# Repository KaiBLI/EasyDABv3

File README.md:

# EasyDABv3
Prototype EasyDABv3 Board Map and Schematic

This is an unfinished prototype and we are missing firmware for the SoC and FPGA for this project. I am uploading this here for preservation in case anyone fancies a go at resolving the existing issues with this prototype and to design firmware. 

Even with the original firmware for this board, there are existing incompatibilities between the FPGA and the SoC that may cause some 'problems'. If you need a DAB modulator, check out https://github.com/KaiBLI/EasyDABv2 

Board Design and Photos Credit to Sergiy https://tipok.org.ua/

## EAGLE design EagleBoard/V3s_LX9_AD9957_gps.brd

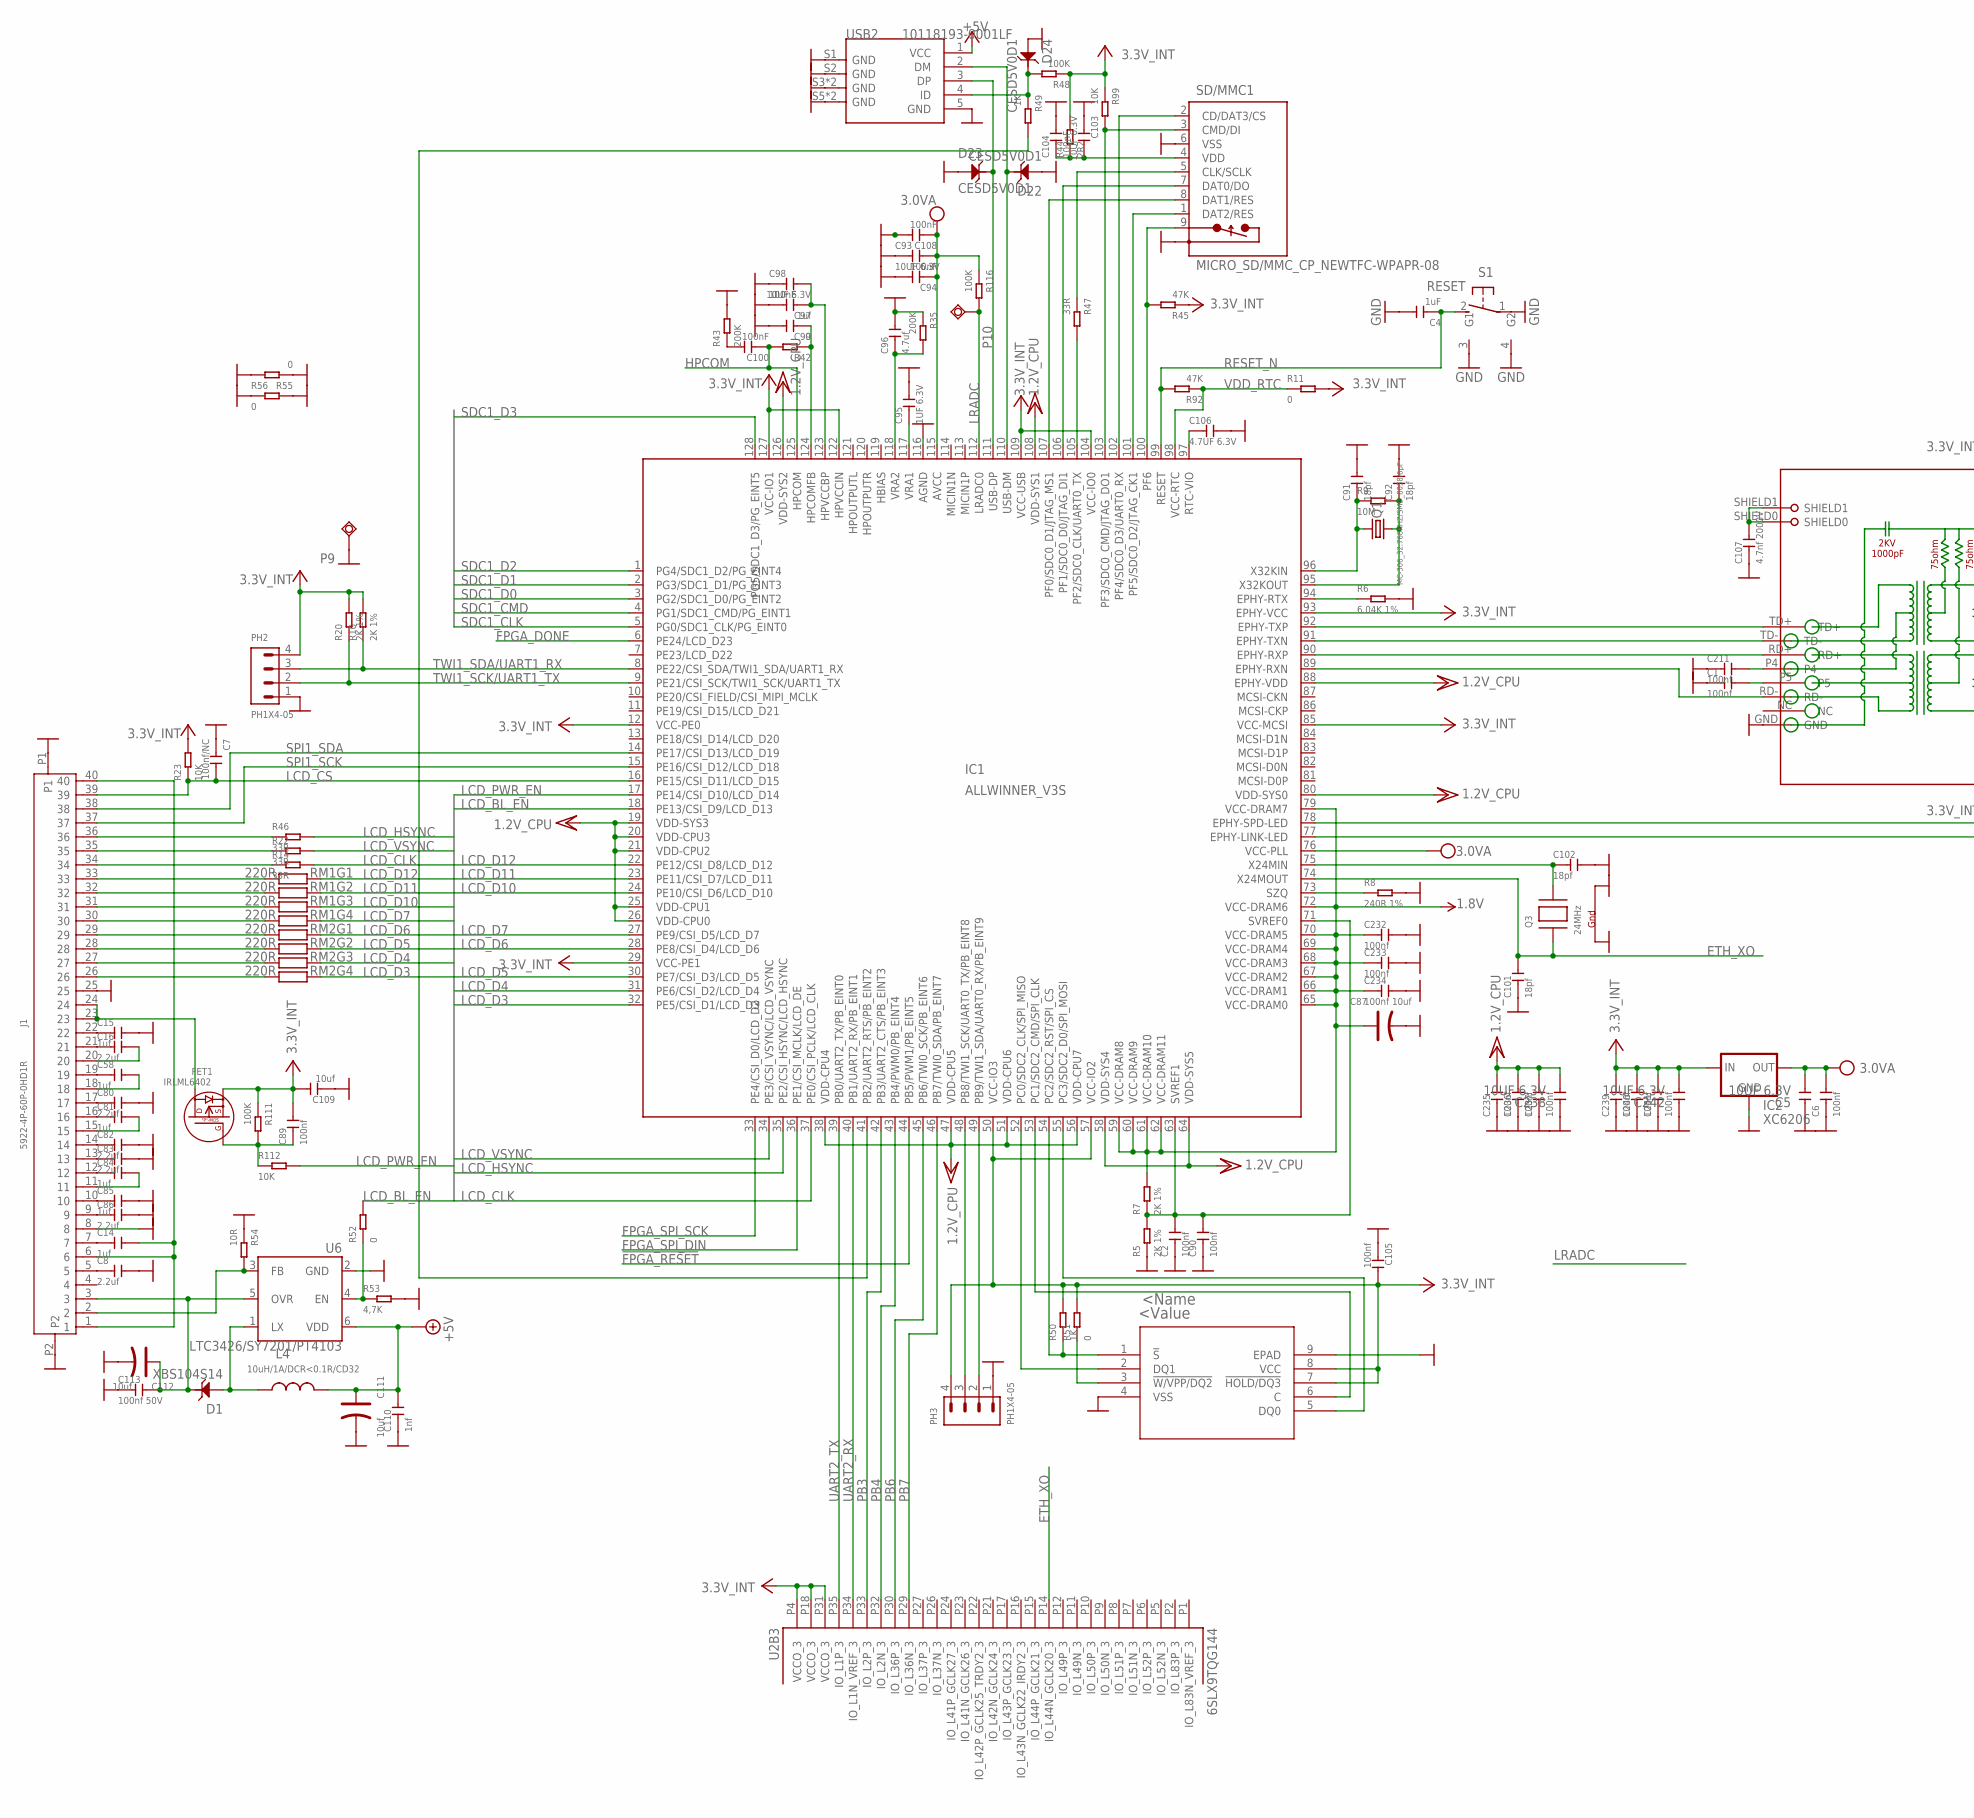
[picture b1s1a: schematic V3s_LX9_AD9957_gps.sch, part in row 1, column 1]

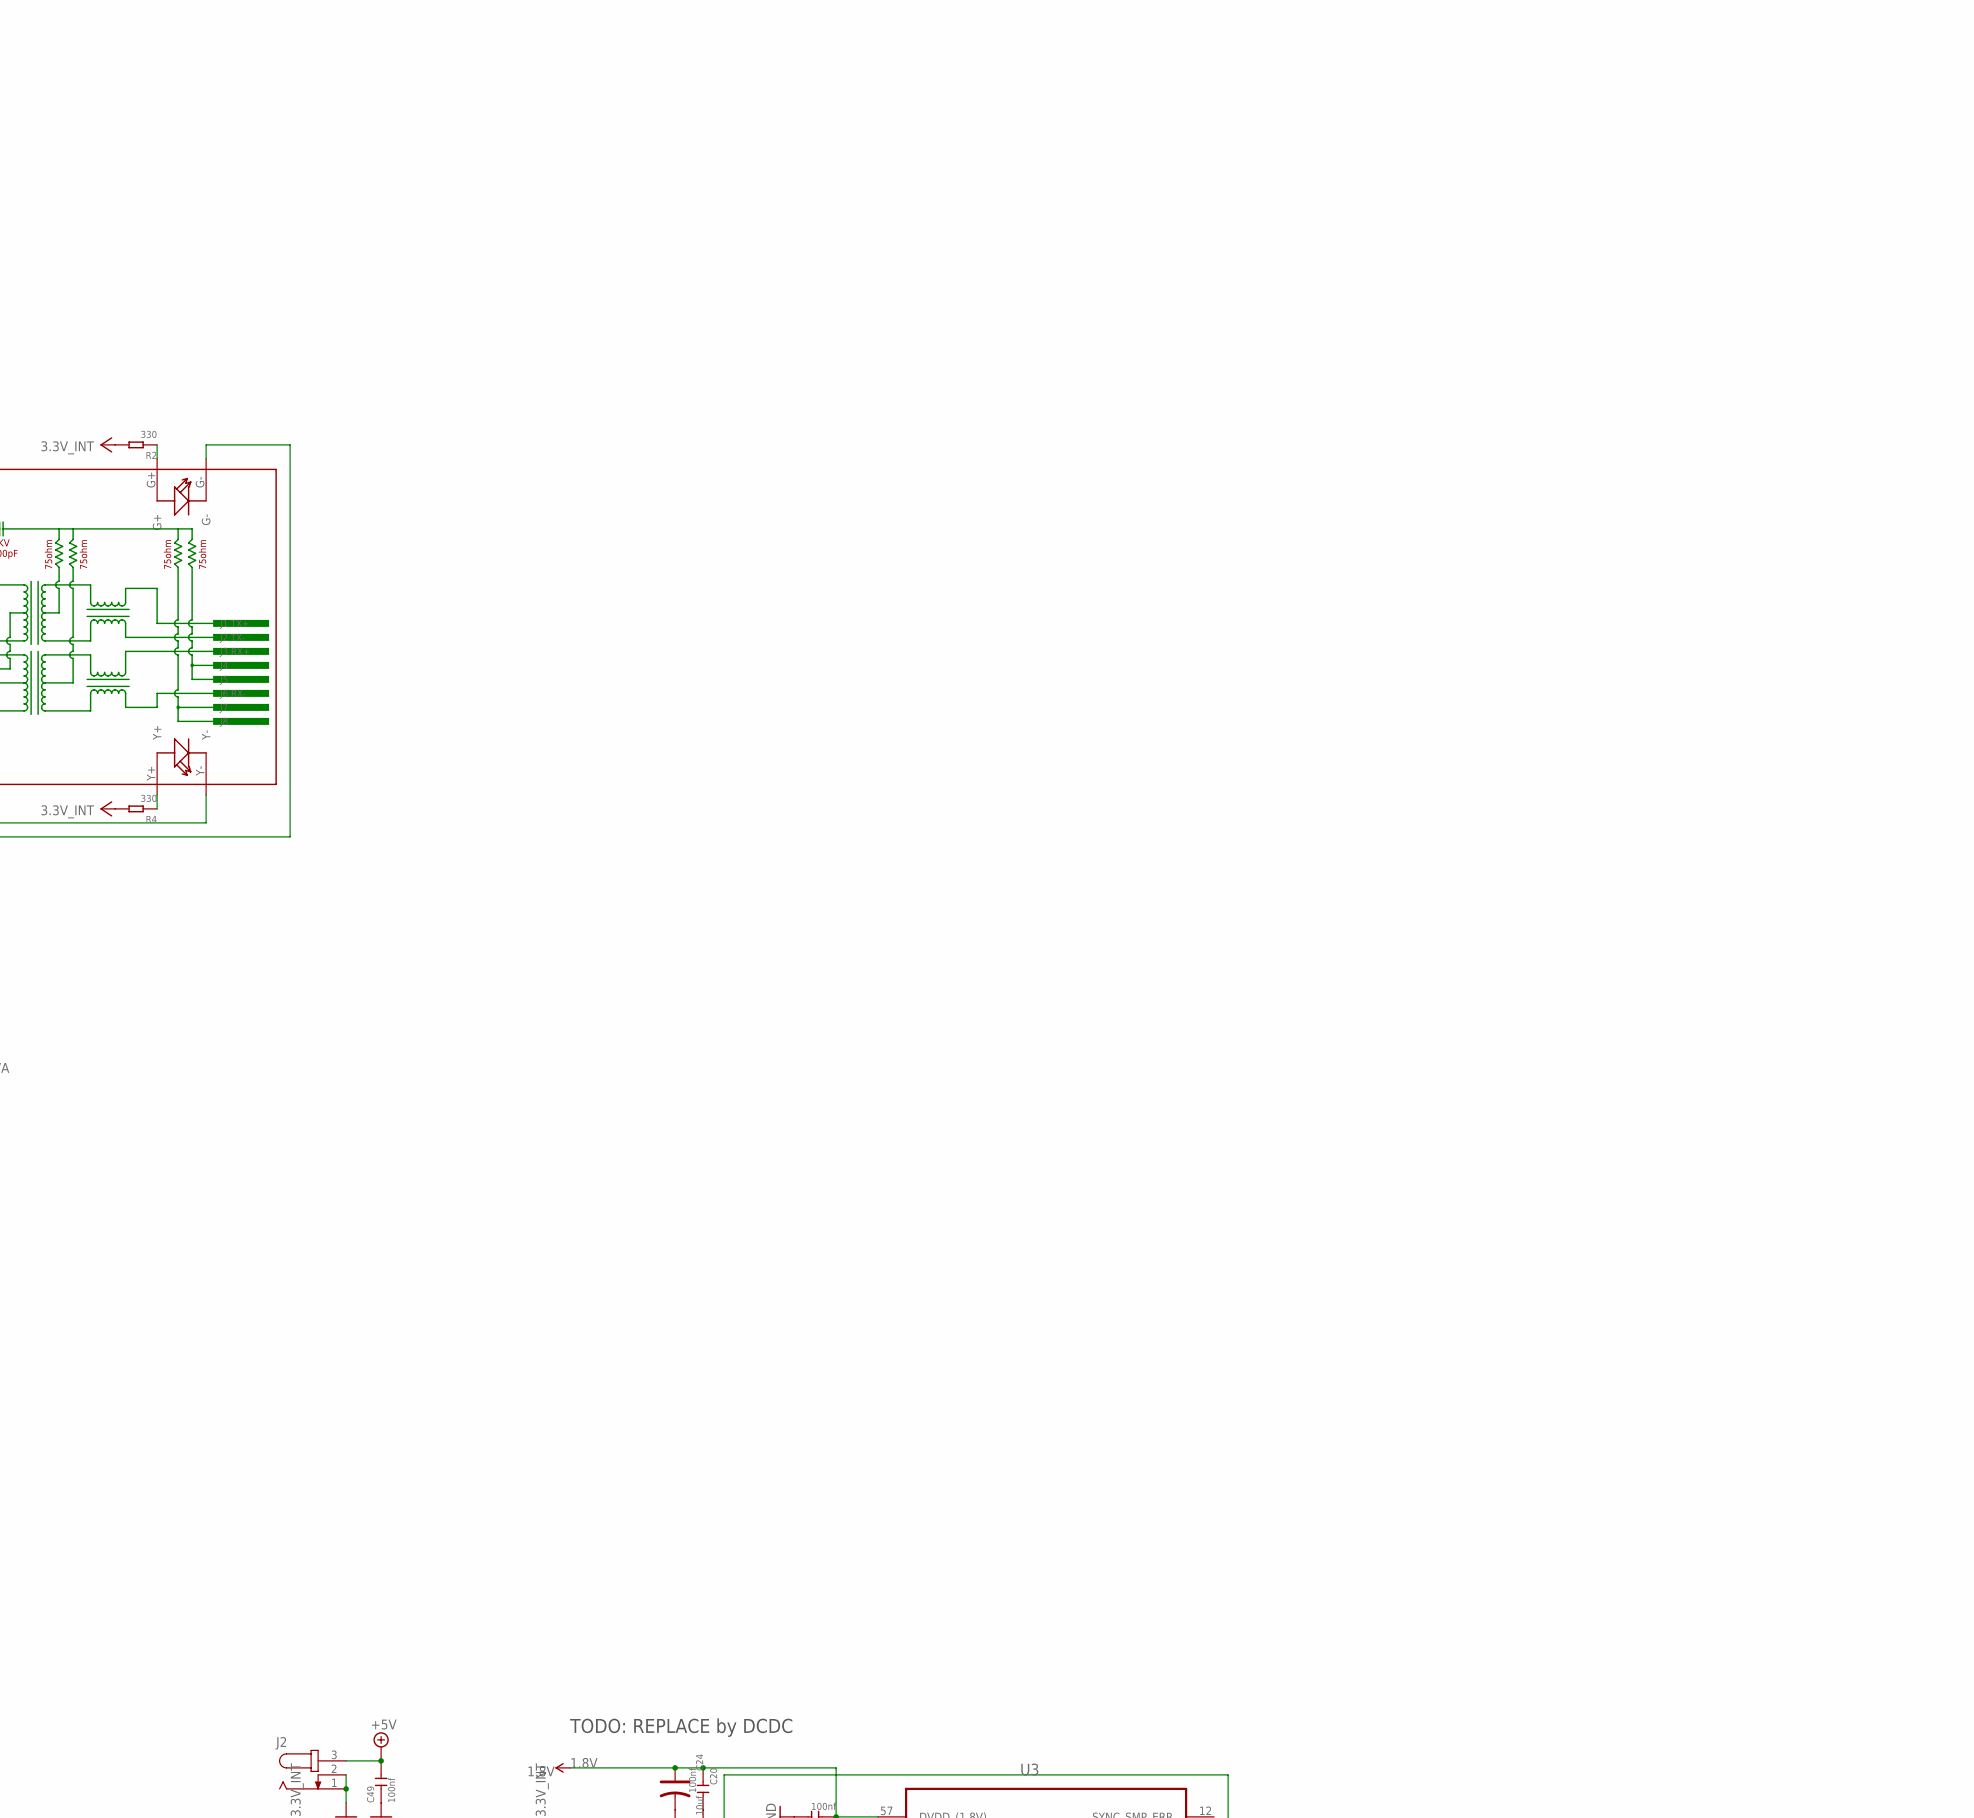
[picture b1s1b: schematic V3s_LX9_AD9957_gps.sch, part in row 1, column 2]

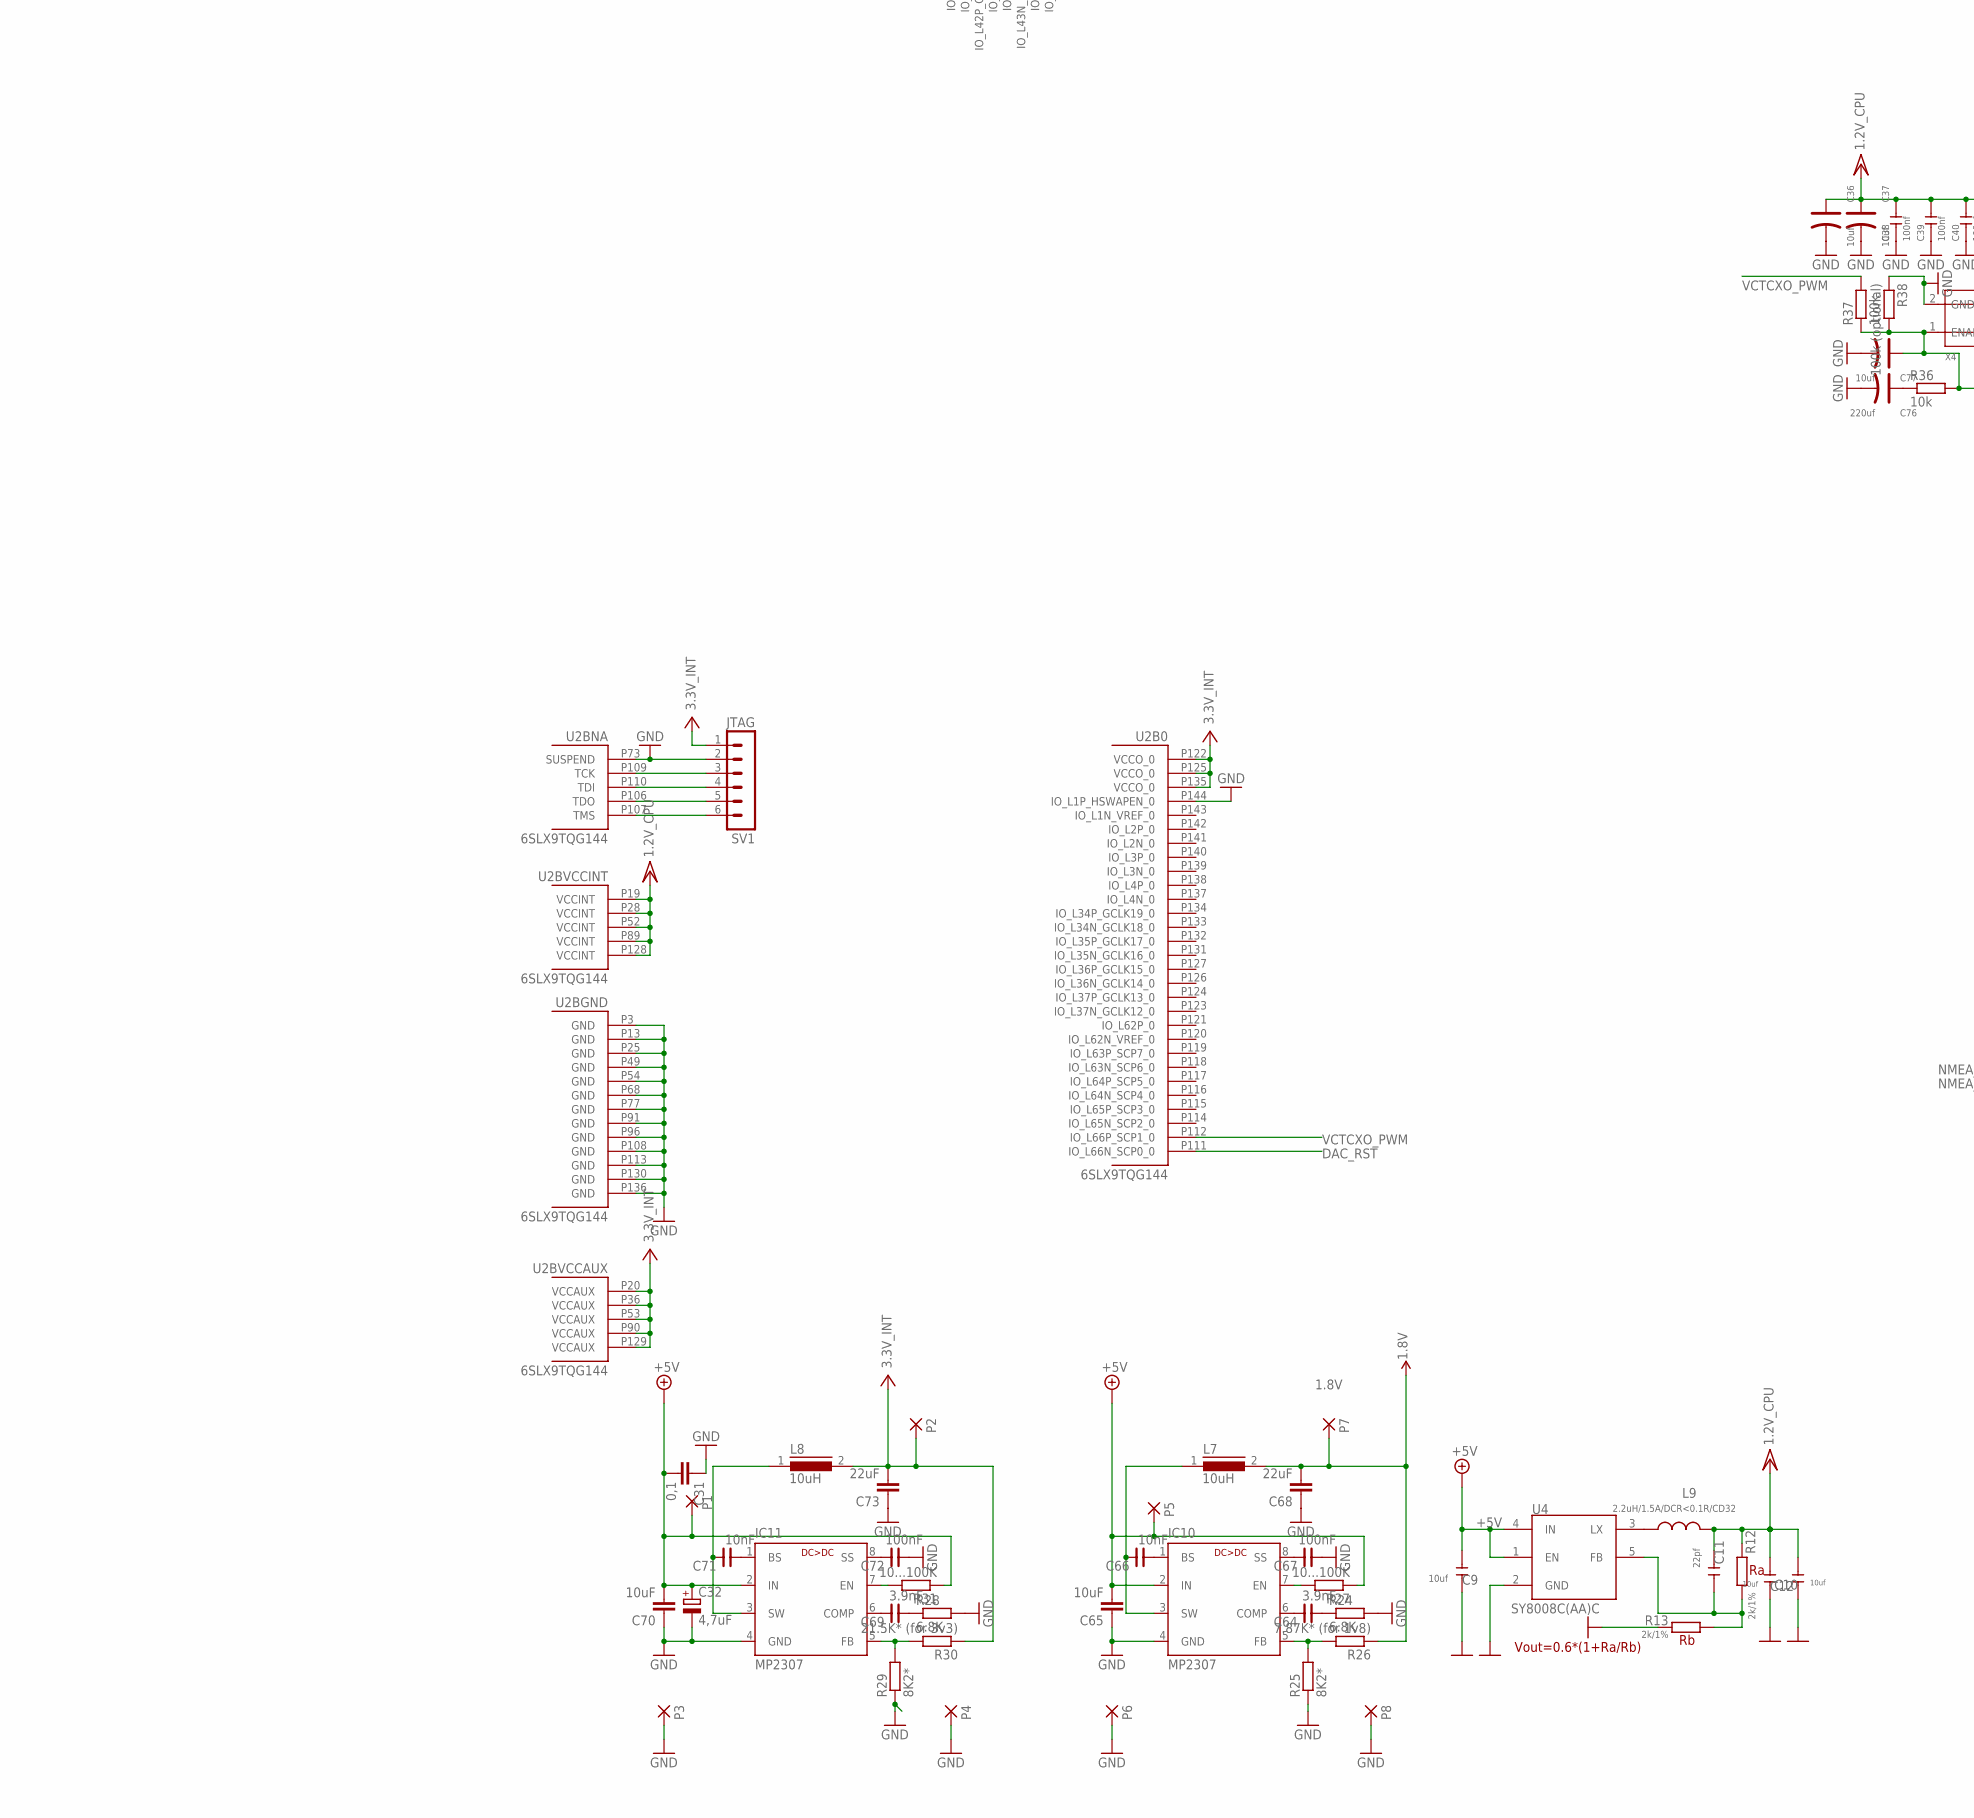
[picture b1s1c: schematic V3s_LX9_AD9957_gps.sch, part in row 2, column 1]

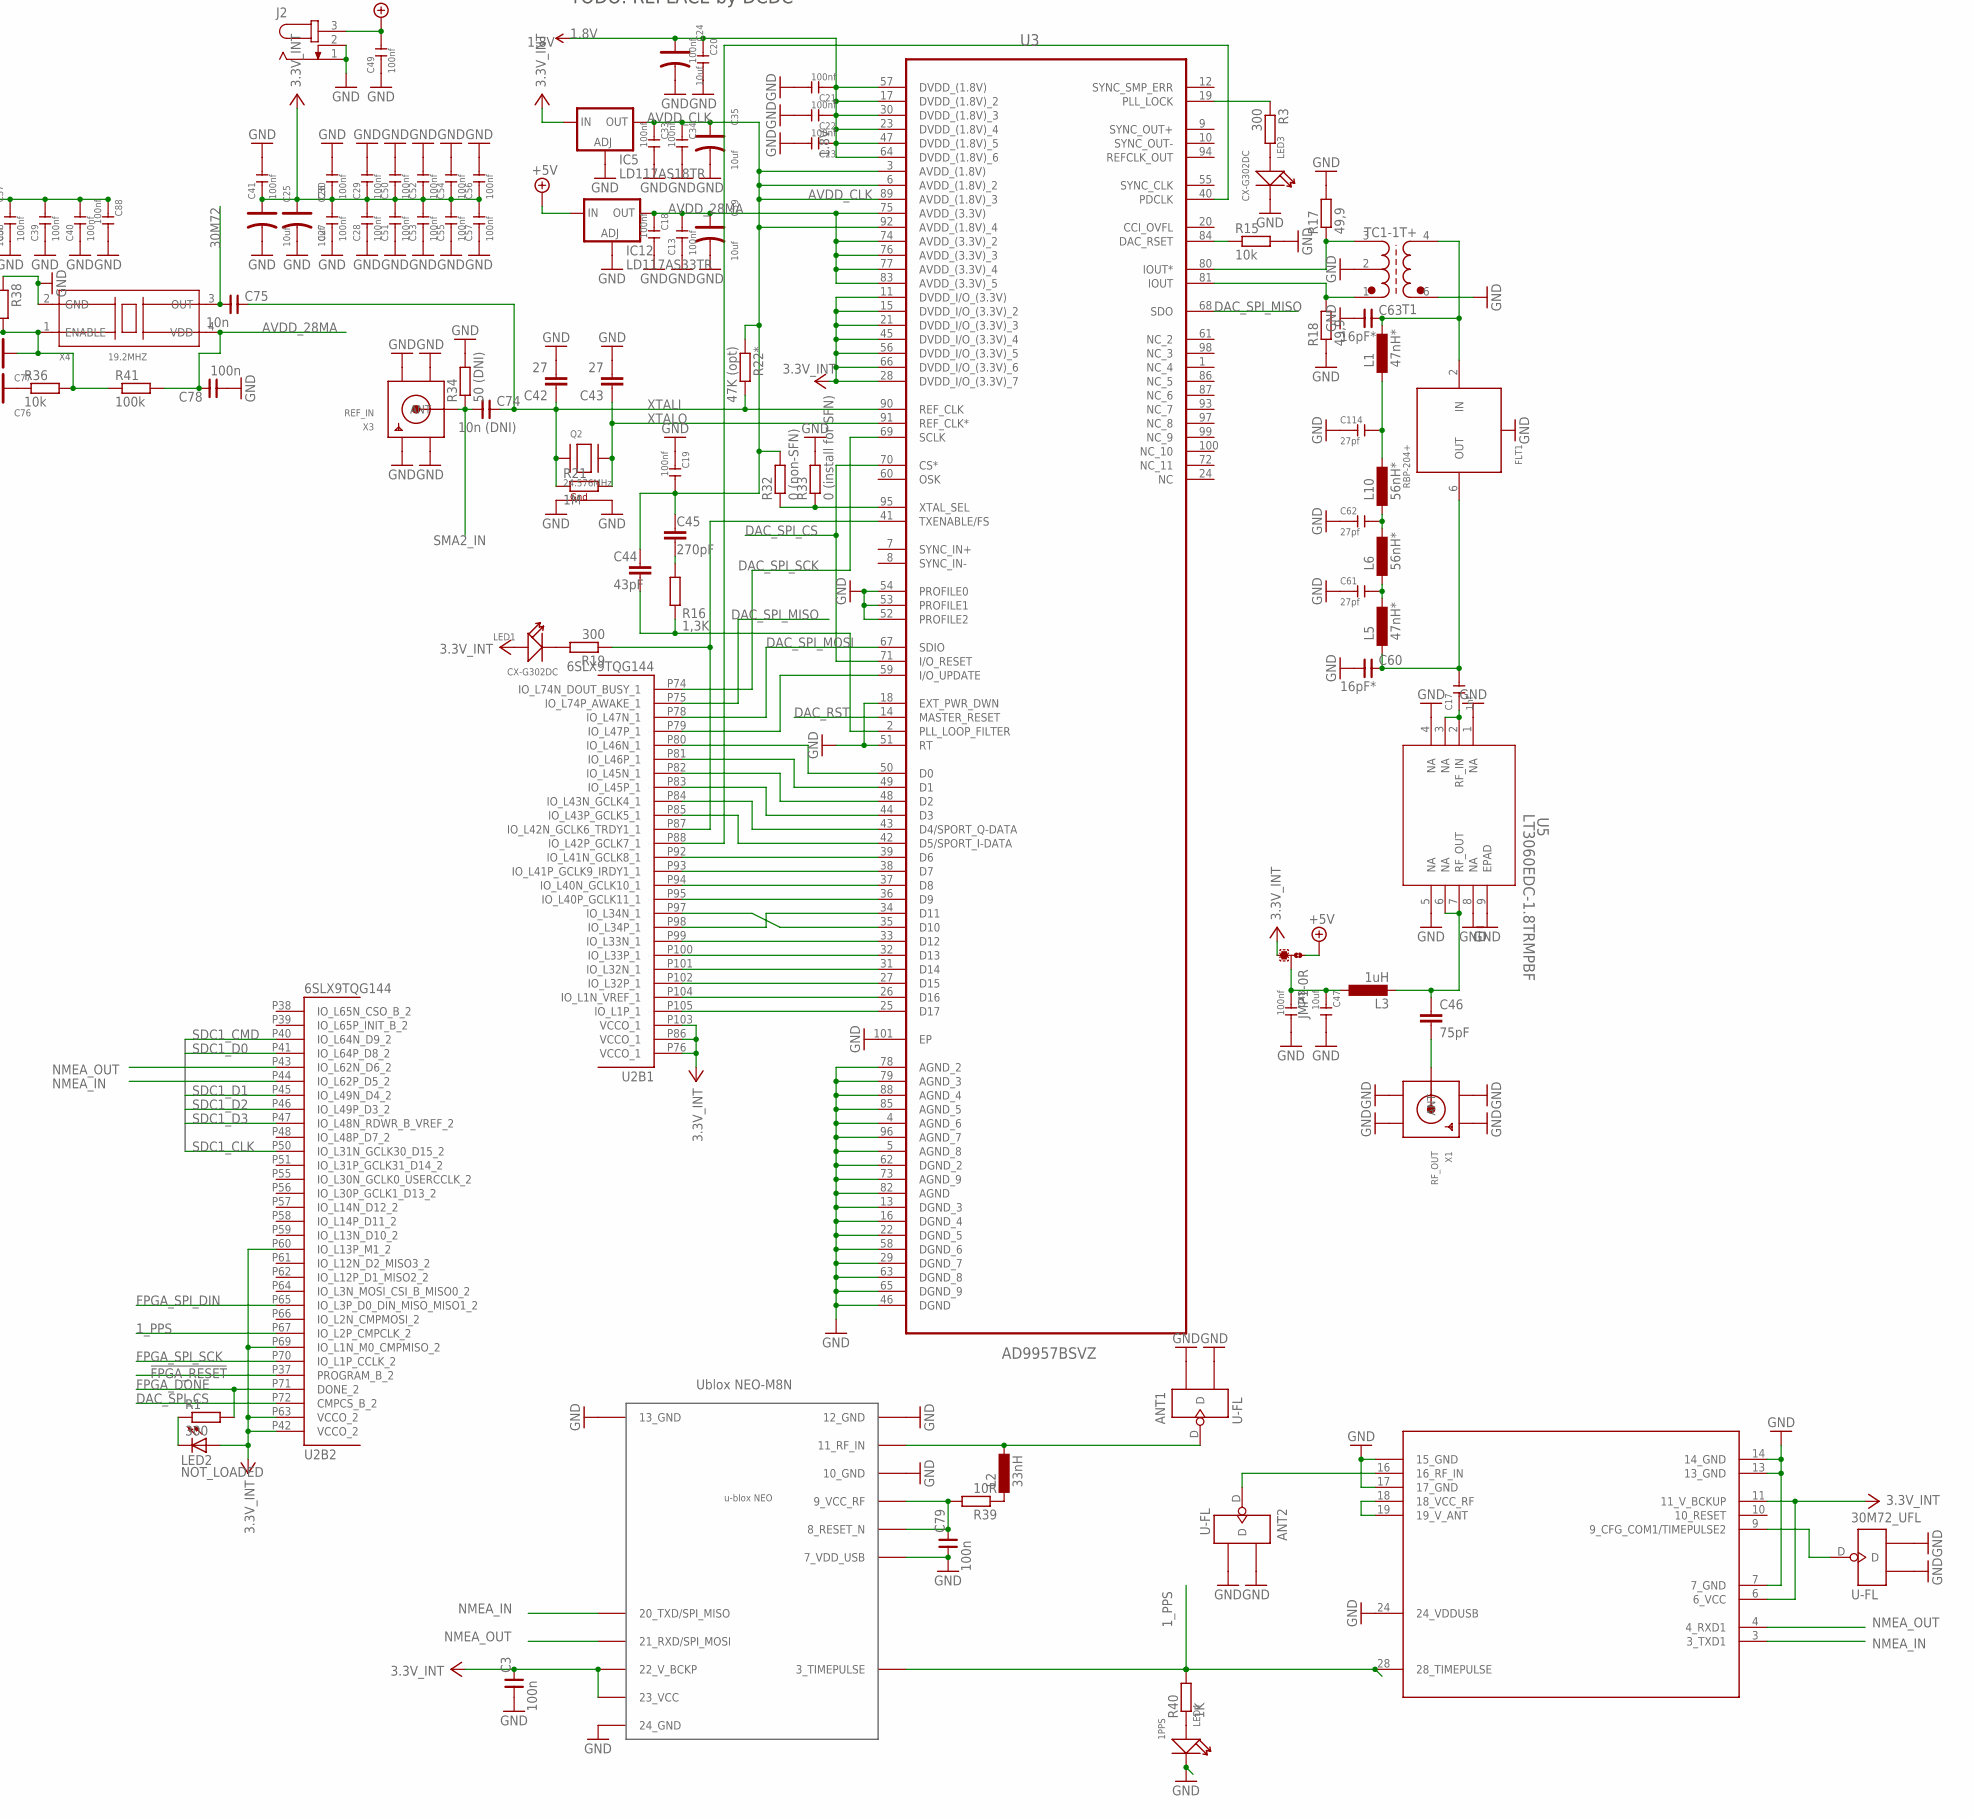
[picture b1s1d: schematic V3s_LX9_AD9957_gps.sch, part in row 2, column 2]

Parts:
30M72_UFL: U-FL; U-FL3P-SMD-2.6X2.6X1.0MM
ANT1, ANT2: U-FL; U-FL3P-SMD-2.6X2.6X1.0MM
C1, C2, C6, C23, C30, C38, C39, C40, C50, C52, C53, C55, C56, C88, C89, C90, C105, C211, C232, C233, C234, C235, C236, C237, C239, C240, C241: 100nf; C0603
C3, C78, C79: 100n; 0603
C4: 1uF; C0603
C5, C93, C97, C103, C238, C242: 10UF 6.3V; C0603
C7: 100nf/NC; C0603
C8, C16, C80, C82, C83, C86: 2.2uf; C0603
C9, C10, C12: 10uf; C0603
C11: 22pf; C0603
C13, C18, C19, C20, C21, C22, C27, C28, C29, C33, C34, C41, C48, C49, C51, C54, C57: 100nf; C0805
C14, C15, C58, C81, C84, C85, C99: 1uf; C0603
C17, C110: 1nf; C0603
C24, C25, C26, C35, C36, C37, C59, C77, C87, C111, C112: 10uf; AVX-A
C31: 0,1; C0805
C32: 4,7uF; A/3216-18R
C42, C43: 27; C0805
C44: 43pF; C0805
C45: 270pF; C0805
C46: 75pF; C0805
C47, C109: 10uf; C0805
C60, C63: 16pF*; 0603
C61, C62, C114: 27pf; C0603
C64, C69: 3.9nF; 0603
C65, C70: 10uF; C1206
C66, C71: 10nF; 0603
C67, C72: 100nF; 0603
C68, C73: 22uF; C1206
C74: 10n (DNI); 0603
C75: 10n; 0603
C76: 220uf; AVX-D
C91, C92, C101, C102: 18pf; C0603
C94, C98, C100, C104, C108: 100nF; C0603
C95: 1UF 6.3V; C0603
C96: 4.7uf; C0603
C106: 4.7UF 6.3V; C0603
C107: 4.7nf 2000V; C1206
C113: 100nf 50V; C0603
D1: XBS104S14; SOD-123
D22, D23, D24: CESD5V0D1; SOD-123
FET1: IRLML6402; SOT23
FLT1: RBP-204+; GP731
IC1: ALLWINNER_V3S; ELQFP128
IC2: XC6206; SOT23
IC5: LD117AS18TR; SOT223
IC10, IC11: MP2307; SO8
IC12: LD117AS33TR; SOT223
J1: 5922-4P-60P-0HD1R; FPCE40-SMD-0.5-90D
J2: JACK-PLUG0; SPC4077
JMP1: 0R-JUMPA; A0R-JMP
L1, L5: 47nH*; INDC1608X95N
L2: 33nH; INDC1608X95N
L3: 1uH; L3216C
L4: 10uH/1A/DCR<0.1R/CD32; CD32
L6, L10: 56nH*; INDC1608X95N
L7, L8: 10uH; DR74
L9: 2.2uH/1.5A/DCR<0.1R/CD32; CD32
LED1, LED3: CX-G302DC; LED2-2.54-D3.0MM
LED2: NOT_LOADED; CHIPLED_1206
LED4: 1PPS; LED2-2.54-D3.0MM
P1, P2, P3, P4, P5, P6, P7, P8: 1,6/0,8
P9, P10: TESTPADTESTPAD30/30; TESTPAD_30-ROUND
PH2, PH3: PH1X4-05; PH005-1-4
Q1: MC-306_32.768KHZ/SMD_8038/6pF; MC-306
Q2: 24.576MHz; NX3225
Q3: 24MHz; NX3225
R1, R3, R19: 300; M0805
R2, R4: 330; R0603
R5, R7, R10, R20: 2K 1%; R0603
R6: 6.04K 1%; R0603
R8: 240R 1%; R0603
R9: 10M; R0603
R11, R42, R51, R52, R55, R56: 0; R0603
R12, R13: 2k/1%; R0603_5MIL_DWS
R14, R22, R46, R47: 33R; R0603
R15: 10k; R0805
R16: 1,3K; R0805
R17, R18: 49,9; R0805
R21: 1M; R0805
R22*: 47K (opt); R0603
R23: 10K; R0402
R24, R28: 6.8K; R0603
R25, R29: 8K2*; R0603
R26: 7.87K* (for 1v8); R0603
R27, R31: 10...100K; R0603
R30: 21.5K* (for 3v3); R0603
R32: 0 (non-SFN); R0402
R33: 0 (install for SFN); R0402
R34: 50 (DNI); R0402
R35, R43: 200K; R0603
R36: 10k; R0603
R37, R41: 100k; R0603
R38: 100k (optional); R0603
R39: 10R; R0402
R40: 1K; R0402
R44: 2R2; R0603
R45, R92: 47K; R0603
R48, R111, R116: 100K; R0603
R49, R50: 1K; R0603
R53: 4,7K; R0603
R54: 10R; R0603
R99, R112: 10K; R0603
RJ1: HR911105A
RM1, RM2: 220R; R_MATRIX_4_0402_25X625
S1: RESET; B3F-31XX
SD/MMC1: MICRO_SD/MMC_CP_NEWTFC-WPAPR-08; TFC-WPAPR-08
SV1: JTAG; MA06-1
T1: TC1-1T+; AT224-3
U1: N25Q256A13EF840EMIC; MIC-VFDFPN-8_8X6-M
U2: 6SLX9TQG144; TQ144
U3: AD9957BSVZ; QFP50P1600X1600X120-101N
U4: SY8008C(AA)C; SOT23-5
U5: LT3060EDC-1.8TRMPBF; DFN-8_DC
U6: LTC3426/SY7201/PT4103; SOT23-6
U10: NEO-M8
U11: UBLOX_LEA-6; UBLOX_LEA-6T
USB2: 10118193-0001LF; MICRO-USB5+6P-SMD-0.65-B
X1: RF_OUT; SMA90_DIP
X3: REF_IN; W5500_LX9_AD9957_SMA_EDGELAUNCH_UFL
X4: 19.2MHZ; X4-SMD-3.2X2.5X0.7MM

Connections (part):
1.8V: C20.1, C21.1, C22.1, C23.1, C24.+, C68.2, C87.+, C232.1, C233.1, C234.1, IC1.59 (VCC-DRAM8), IC1.60 (VCC-DRAM9), IC1.61 (VCC-DRAM10), IC1.62 (VCC-DRAM11), IC1.65 (VCC-DRAM0), IC1.66 (VCC-DRAM1), IC1.67 (VCC-DRAM2), IC1.68 (VCC-DRAM3), IC1.69 (VCC-DRAM4), IC1.70 (VCC-DRAM5), IC1.72 (VCC-DRAM6), IC1.79 (VCC-DRAM7), L7.2, P7.1, R7.2, R26.1, U3.17 (DVDD_(1.8V)_2), U3.23 (DVDD_(1.8V)_4), U3.30 (DVDD_(1.8V)_3), U3.47 (DVDD_(1.8V)_5), U3.57 (DVDD_(1.8V)), U3.64 (DVDD_(1.8V)_6)
1_PPS: R40.2, U2.P67 (IO_L2P_CMPCLK_2), U10.3 (3_TIMEPULSE), U11.28 (28_TIMEPULSE)
30M72: C75.1, X4.3 (OUT)
!FPGA_RESET: IC1.44 (PB5/PWM1/PB_EINT5), U2.P37 (PROGRAM_B_2)
+5V: C9.1, C31.2, C32.+, C49.2, C65.2, C70.2, C110.2, C111.+, IC10.2 (IN), IC11.2 (IN), IC12.3 (IN), J2.3, JMP1.1, L4.1, P1.1, P5.1, R27.1, R31.1, U4.1 (EN), U4.4 (IN), U6.6 (VDD), USB2.1 (VCC)
AVDD_28MA: C13.2, C18.1, C59.+, C78.2, IC12.4 (OUT), R41.2, U3.74 (AVDD_(3.3V)_2), U3.75 (AVDD_(3.3V)), U3.76 (AVDD_(3.3V)_3), U3.77 (AVDD_(3.3V)_4), U3.83 (AVDD_(3.3V)_5), X4.4 (VDD)
AVDD_CLK: C19.2, C33.1, C34.1, C35.+, C44.1, C45.1, IC5.4 (OUT), R22*.1, R32.2, U3.3 (AVDD_(1.8V)), U3.6 (AVDD_(1.8V)_2), U3.89 (AVDD_(1.8V)_3), U3.92 (AVDD_(1.8V)_4)
DAC_RST: U2.P111 (IO_L66N_SCP0_0), U3.14 (MASTER_RESET)
DAC_SPI_CS: U2.P72 (CMPCS_B_2), U3.70 (CS*), U3.71 (I/O_RESET)
DAC_SPI_MISO: U2.P75 (IO_L74P_AWAKE_1), U3.68 (SDO)
DAC_SPI_MOSI: U2.P78 (IO_L47N_1), U3.67 (SDIO)
DAC_SPI_SCK: U2.P74 (IO_L74N_DOUT_BUSY_1), U3.69 (SCLK)
ETH_XO: C101.2, IC1.74 (X24MOUT), Q3.1 (X1), U2.P14 (IO_L44N_GCLK20_3)
FPGA_DONE: IC1.6 (PE24/LCD_D23), R1.2, U2.P71 (DONE_2)
FPGA_SPI_DIN: IC1.36 (PE1/CSI_MCLK/LCD_DE), U2.P65 (IO_L3P_D0_DIN_MISO_MISO1_2)
FPGA_SPI_SCK: IC1.33 (PE4/CSI_D0/LCD_D2), U2.P70 (IO_L1P_CCLK_2)
GND: 30M72_UFL.GND1, 30M72_UFL.GND2, ANT1.GND1, ANT1.GND2, ANT2.GND1, ANT2.GND2, C1.1, C2.1, C3.1, C4.2, C5.1, C6.1, C7.1, C8.2, C9.2, C10.2, C12.2, C13.1, C15.2, C18.2, C19.1, C20.2, C21.2, C22.2, C23.2, C24.-, C25.-, C26.-, C27.1, C28.1, C29.2, C30.2, C31.1, C32.-, C33.2, C34.2, C35.-, C36.-, C37.-, C38.1, C39.1, C40.1, C41.2, C42.2, C43.2, C47.2, C48.2, C49.1, C50.2, C51.1, C52.2, C53.1, C54.2, C55.1, C56.2, C57.1, C59.-, C60.1, C61.1, C62.1, C63.1, C65.1, C67.1, C68.1, C70.1, C72.1, C73.1, C76.-, C77.-, C78.1, C79.1, C80.2, C82.2, C83.2, C85.2, C86.2, C87.-, C88.2, C90.1, C91.2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
GPSDO_OUT_30M72: 30M72_UFL.D, U11.9 (9_CFG_COM1/TIMEPULSE2)
HPCOM: C100.1, IC1.125 (HPCOM), R42.2
LCD_BL_EN: IC1.18 (PE13/CSI_D9/LCD_D13), R52.2
LCD_CLK: IC1.37 (PE0/CSI_PCLK/LCD_CLK), R14.2
LCD_CS: C7.2, IC1.16 (PE15/CSI_D11/LCD_D15), J1.39, R23.1
LCD_D3: IC1.32 (PE5/CSI_D1/LCD_D3), RM2.4.1 (1)
LCD_D4: IC1.31 (PE6/CSI_D2/LCD_D4), RM2.3.1 (1)
LCD_D5: IC1.30 (PE7/CSI_D3/LCD_D5), RM2.2.1 (1)
LCD_D6: IC1.28 (PE8/CSI_D4/LCD_D6), RM2.1.1 (1)
LCD_D7: IC1.27 (PE9/CSI_D5/LCD_D7), RM1.4.1 (1)
LCD_D10: IC1.24 (PE10/CSI_D6/LCD_D10), RM1.3.1 (1)
LCD_D11: IC1.23 (PE11/CSI_D7/LCD_D11), RM1.2.1 (1)
LCD_D12: IC1.22 (PE12/CSI_D8/LCD_D12), RM1.1.1 (1)
LCD_HSYNC: IC1.35 (PE2/CSI_HSYNC/LCD_HSYNC), R46.2
LCD_PWR_EN: IC1.17 (PE14/CSI_D10/LCD_D14), R112.2
LCD_VSYNC: IC1.34 (PE3/CSI_VSYNC/LCD_VSYNC), R22.2
LRADC: IC1.112 (LRADC0), P10.1, R116.2
unnamed: SV1.6, U2.P107 (TMS)
unnamed: SV1.5, U2.P106 (TDO)
unnamed: SV1.4, U2.P110 (TDI)
unnamed: SV1.3, U2.P109 (TCK)
unnamed: LED2.C, R1.1
unnamed: C62.2, L6.2, L10.1
unnamed: U2.P105 (IO_L1P_1), U3.25 (D17)
unnamed: C14.2, J1.1, J1.6, J1.40
unnamed: U2.P88 (IO_L42P_GCLK7_1), U3.40 (PDCLK)
unnamed: R19.1, U2.P87 (IO_L42N_GCLK6_TRDY1_1), U3.41 (TXENABLE/FS)
unnamed: U2.P85 (IO_L43P_GCLK5_1), U3.42 (D5/SPORT_I-DATA)
unnamed: U2.P84 (IO_L43N_GCLK4_1), U3.43 (D4/SPORT_Q-DATA)
unnamed: U2.P83 (IO_L45P_1), U3.44 (D3)
unnamed: U2.P82 (IO_L45N_1), U3.48 (D2)
unnamed: U2.P92 (IO_L41N_GCLK8_1), U3.39 (D6)
unnamed: U2.P93 (IO_L41P_GCLK9_IRDY1_1), U3.38 (D7)
unnamed: U2.P94 (IO_L40N_GCLK10_1), U3.37 (D8)
unnamed: U2.P95 (IO_L40P_GCLK11_1), U3.36 (D9)
unnamed: U2.P98 (IO_L34P_1), U3.34 (D11)
unnamed: U2.P97 (IO_L34N_1), U3.35 (D10)
unnamed: U2.P99 (IO_L33N_1), U3.33 (D12)
unnamed: U2.P100 (IO_L33P_1), U3.32 (D13)
unnamed: U2.P101 (IO_L32N_1), U3.31 (D14)
unnamed: U2.P102 (IO_L32P_1), U3.27 (D15)
unnamed: U2.P104 (IO_L1N_VREF_1), U3.26 (D16)
unnamed: U2.P79 (IO_L47P_1), U3.59 (I/O_UPDATE)
unnamed: C14.1, J1.7
unnamed: U2.P81 (IO_L46P_1), U3.49 (D1)
unnamed: LED3.A (+), R3.2
unnamed: R3.1, U3.19 (PLL_LOCK)
unnamed: R15.1, U3.84 (DAC_RSET)
unnamed: R17.1, T1.3 (S), U3.80 (IOUT*)
unnamed: R18.2, T1.1 (SD), U3.81 (IOUT)
unnamed: C63.2, FLT1.2 (IN), L1.2, T1.4
unnamed: U2.P80 (IO_L46N_1), U3.50 (D0)
unnamed: IC1.89 (EPHY-RXN), RJ1.RD-
unnamed: C211.2, RJ1.P4
unnamed: IC1.94 (EPHY-RTX), R6.1
unnamed: IC1.78 (EPHY-SPD-LED), RJ1.Y-
unnamed: IC1.77 (EPHY-LINK-LED), RJ1.G-
unnamed: R4.1, RJ1.Y+
unnamed: R2.1, RJ1.G+
unnamed: C2.2, C90.2, IC1.63 (SVREF1), IC1.71 (SVREF0), R5.2, R7.1
unnamed: IC1.73 (SZQ), R8.1
unnamed: C92.1, IC1.95 (X32KOUT), Q1.1, R9.2
unnamed: C91.1, IC1.96 (X32KIN), Q1.4 (2), R9.1
unnamed: D22.- (2), IC1.110 (USB-DM), USB2.2 (DM)
unnamed: D23.- (2), IC1.111 (USB-DP), USB2.3 (DP)
unnamed: C95.1, IC1.117 (VRA1)
unnamed: C96.1, IC1.118 (VRA2), R35.2
unnamed: C99.1, IC1.124 (HPCOMFB), R42.1
unnamed: C102.1, IC1.75 (X24MIN), Q3.3 (X2)
unnamed: U11.18 (18_VCC_RF), U11.19 (19_V_ANT)
unnamed: IC1.107 (PF0/SDC0_D1/JTAG_MS1), SD/MMC1.8 (DAT1/RES)
unnamed: IC1.106 (PF1/SDC0_D0/JTAG_DI1), SD/MMC1.7 (DAT0/DO)
unnamed: R47.1, SD/MMC1.5 (CLK/SCLK)
unnamed: IC1.103 (PF3/SDC0_CMD/JTAG_DO1), R99.2, SD/MMC1.3 (CMD/DI)
unnamed: IC1.102 (PF4/SDC0_D3/UART0_RX), SD/MMC1.2 (CD/DAT3/CS)
unnamed: IC1.101 (PF5/SDC0_D2/JTAG_CK1), SD/MMC1.1 (DAT2/RES)
unnamed: IC1.100 (PF6), R45.2, SD/MMC1.9 (CP_E)
unnamed: ANT1.D, L2.2, U10.11 (11_RF_IN)
unnamed: IC1.105 (PF2/SDC0_CLK/UART0_TX), R47.2
unnamed: D24.- (2), R48.2, R49.1, USB2.4 (ID)
unnamed: IC1.41 (PB2/UART2_RTS/PB_EINT2), R49.2
unnamed: IC1.92 (EPHY-TXP), RJ1.TD+
unnamed: IC1.91 (EPHY-TXN), RJ1.TD-
unnamed: IC1.90 (EPHY-RXP), RJ1.RD+
unnamed: L9.1, U4.3 (LX)
unnamed: C97.1, C98.2, IC1.123 (HPVCCBP)
unnamed: C8.1, J1.5
unnamed: R51.1, U1.3 (!W/VPP/DQ2)
unnamed: C11.2, R12.2, R13.1, U4.5 (FB)
unnamed: J1.33, RM1.1.2 (2)
unnamed: ANT2.D, U11.16 (16_RF_IN)
unnamed: C114.2, L1.1, L10.2
unnamed: C44.2, R16.2, U3.2 (PLL_LOOP_FILTER)
unnamed: J1.36, R46.1
unnamed: J1.35, R22.1
unnamed: J1.34, R14.1
unnamed: J1.32, RM1.2.2 (2)
unnamed: J1.31, RM1.3.2 (2)
unnamed: J1.30, RM1.4.2 (2)
unnamed: C45.2, R16.1
unnamed: C17.2, C60.2, FLT1.6 (OUT), L5.1
unnamed: J1.29, RM2.1.2 (2)
unnamed: C46.1, L3.2, U5.6 (NA), U5.7 (RF_OUT)
unnamed: C46.2, X1.ANTENNA (ANT)
unnamed: C47.1, C48.1, JMP1.2, L3.1
unnamed: LED1.K (-), R19.2
unnamed: L2.1, R39.1
unnamed: C61.2, L5.2, L6.1
unnamed: J1.28, RM2.2.2 (2)
unnamed: C79.2, R39.2, U10.8 (8_RESET_N), U10.9 (9_VCC_RF)
unnamed: LED4.A (+), R40.1
unnamed: J1.27, RM2.3.2 (2)
unnamed: J1.26, RM2.4.2 (2)
unnamed: C15.1, J1.22
unnamed: C17.1, U5.2 (RF_IN), U5.3 (NA)
unnamed: C64.2, IC10.6 (COMP)
unnamed: C64.1, R24.1
unnamed: C66.1, IC10.1 (BS)
unnamed: C66.2, IC10.3 (SW), L7.1
unnamed: C67.2, IC10.8 (SS)
unnamed: IC10.5 (FB), R25.2, R26.2
unnamed: R32.1, R33.1, U3.95 (XTAL_SEL)
unnamed: IC10.7 (EN), R27.2
unnamed: C100.2, R43.1
unnamed: C69.1, R28.1
unnamed: C69.2, IC11.6 (COMP)
unnamed: C71.1, IC11.1 (BS)
unnamed: C71.2, IC11.3 (SW), L8.1
unnamed: C72.2, IC11.8 (SS)
unnamed: IC11.5 (FB), R29.2, R30.2
unnamed: C103.2, C104.1, R44.1, SD/MMC1.4 (VDD)
unnamed: IC11.7 (EN), R31.2
unnamed: C76.+, R36.1
unnamed: C77.+, R36.2, R37.1, R38.2, R41.1, X4.1 (ENABLE)
unnamed: C16.1, J1.21
unnamed: C16.2, J1.20
unnamed: C58.1, J1.19
unnamed: C58.2, J1.18
unnamed: C80.1, J1.17
unnamed: C81.1, J1.16
unnamed: C81.2, J1.15
unnamed: C82.1, J1.14
unnamed: C83.1, J1.13
unnamed: C84.1, J1.12
unnamed: C84.2, J1.11
unnamed: C85.1, J1.10
unnamed: C86.1, J1.9
unnamed: R52.1, R53.1, U6.4 (EN)
unnamed: D1.+ (1), L4.2, U6.1 (LX)
unnamed: J1.2, R54.2, U6.3 (FB)
unnamed: C112.+, C113.2, D1.- (2), J1.3, U6.5 (OVR)
unnamed: IC1.48 (PB8/TWI1_SCK/UART0_TX/PB_EINT8), PH3.3
unnamed: IC1.49 (PB9/TWI1_SDA/UART0_RX/PB_EINT9), PH3.2
unnamed: IC1.54 (PC2/SDC2_RST/SPI_CS), R50.1, U1.1 (!S)
unnamed: IC1.52 (PC0/SDC2_CLK/SPI_MISO), U1.2 (DQ1)
unnamed: IC1.53 (PC1/SDC2_CMD/SPI_CLK), U1.6 (C)
unnamed: IC1.55 (PC3/SDC2_D0/SPI_MOSI), U1.5 (DQ0)
unnamed: C106.1, IC1.97 (RTC-VIO)
unnamed: C107.2, RJ1.SHIELD0, RJ1.SHIELD1
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
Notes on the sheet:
TODO: REPLACE by DCDC
Ublox NEO-M8N
Vout=0.6*(1+Ra/Rb)

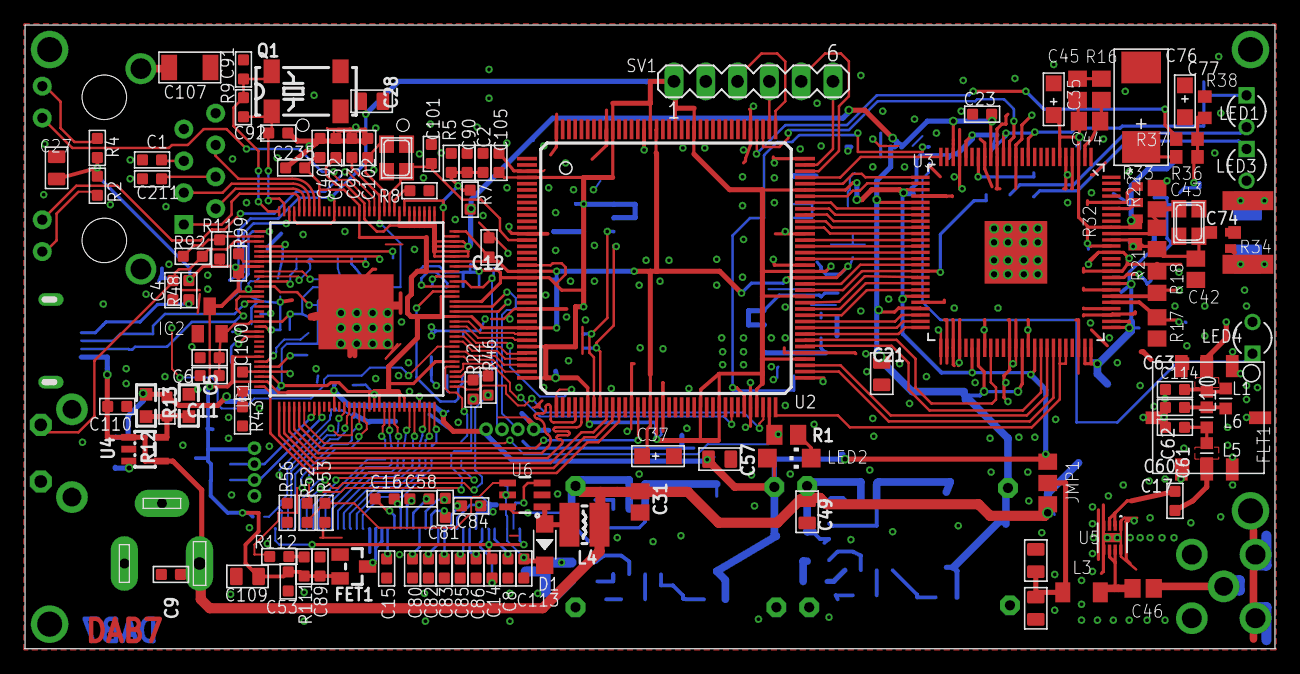
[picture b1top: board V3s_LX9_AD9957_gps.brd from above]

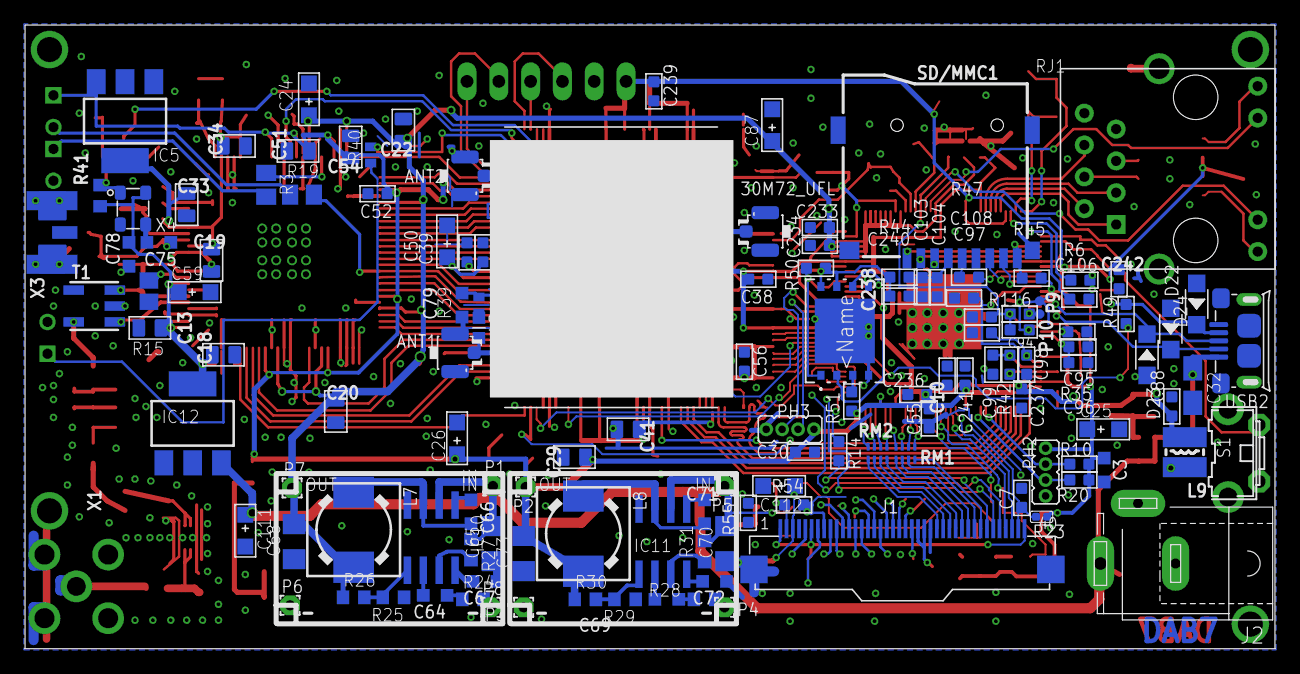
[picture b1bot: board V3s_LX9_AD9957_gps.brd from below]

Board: 2 copper layers, 99.8 x 49.8 mm, 254 parts (134 on the bottom side), 206 nets.

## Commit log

2026-02-23 Create EagleFiles
2026-02-23 Add files via upload
    Adding in EasyDABv3 Boardmap and Schematic
2026-02-23 Uploading Sergiy's EasyDABv3

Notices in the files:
parts and their libraries:
mini-circuits: Copyright (C) 2013, Bob Starr
COPYRIGHT: Copyright C 2015 Accelerated Designs. All rights reserved
SparkFun-Aesthetics: Licensing: Creative Commons ShareAlike 4.0 International - https://creativecommons.org/licenses/by-sa/4.0
